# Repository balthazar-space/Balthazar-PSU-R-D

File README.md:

# Balthazar

Open-hardware laptop computer modules description and concept.

These are electronic schematic modules as presented at https://balthazar.space/wiki/Balthazar with the main aim for team access.
See the [main repository](https://github.com/balthazar-space/balthazar) for other designs.

# Balthazar PSU 

Module BalthazarPSU is a combined battery charger, buck-boost coverter and stereo power amplifier. 
KiCad 5.1.5 files can be found here.

## License

All resources licensed under the CERN Open Hardware Licence CERN-OHL W V.2.0

Version 2.0 of the CERN-OHL introduces three variants of the licence – strongly (S) reciprocal, weakly (W) reciprocal and permissive (P) – which aim to address specific constraints caused by different collaboration models currently used in open-hardware projects. 

The first two variants mean that if any product is made using an open hardware design, the design of that product, including any improvements or modifications, should be made available under the same licence as that of the original product. Permissive licences do not impose this condition.

See the [LICENSE.md](./LICENSE.md) file for more information.

## Funding

This project is funded through the [NGI Zero Entrust Fund](https://nlnet.nl/entrust), a fund
established by [NLnet](https://nlnet.nl) with financial support from the European Commission's
[Next Generation Internet](https://ngi.eu) program. Learn more on the [NLnet project page](https://nlnet.nl/project/Balthazar-Casing/).

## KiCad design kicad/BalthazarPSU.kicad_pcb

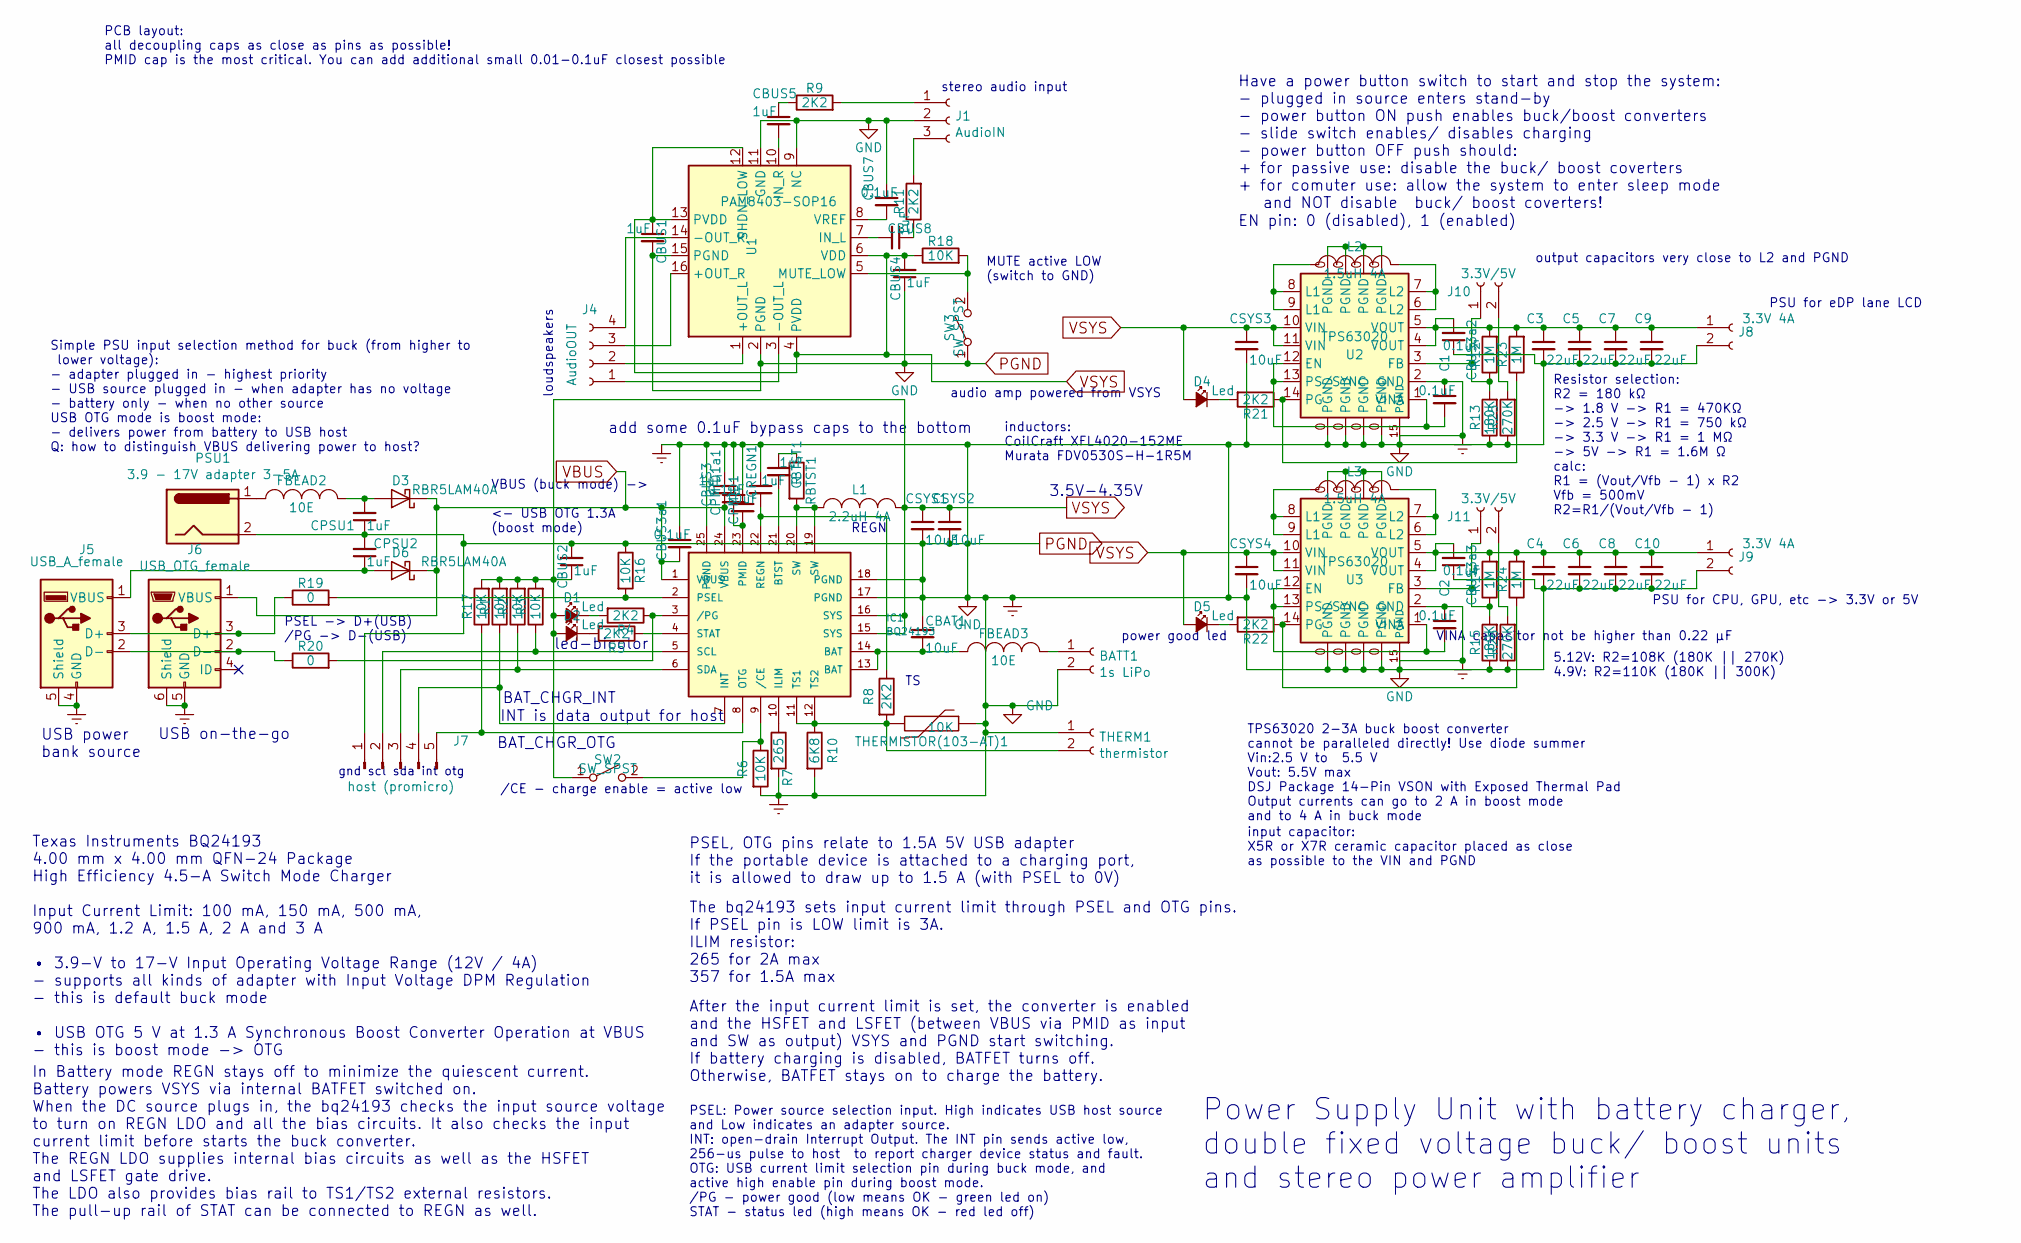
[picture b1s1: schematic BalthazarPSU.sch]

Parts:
BATT1: 1s LiPo; TerminalBlock_bornier-2_P5.08mm
C1, C2: 0.1uF; C_1206_3216Metric
C3, C4, C5, C6, C7, C8, C9, C10: 22uF; C_1206_3216Metric
CBAT1: 10uF; C_1206_3216Metric
CBTST1: 1uF; C_1206_3216Metric
CBUS1, CBUS2, CBUS3, CBUS4, CBUS5, CBUS8: 1uF; C_1206_3216Metric
CBUS3a1, CBUS3a2, CBUS3a3: 0.1uF; C_0805_2012Metric
CBUS7: 0.1uF; C_1206_3216Metric
CPMID1: 10uF; C_1206_3216Metric
CPMID1a1: 0.1uF; C_0805_2012Metric
CPSU1, CPSU2: 1uF; C_1206_3216Metric
CREGN1: 1uF; C_1206_3216Metric
CSYS1, CSYS2, CSYS3, CSYS4: 10uF; C_1206_3216Metric
D1, D2, D4, D5: Led; LED_1206_3216Metric
D3, D6: RBR5LAM40A; D_SOD-128
FBEAD2, FBEAD3: 10E; L_Neosid_MicroCoil_Ms36-L
IC1: BQ24193; QFN-24-1EP_4x4mm_P0.5mm_EP2.7x2.7mm_ThermalVias
J1: AudioIN; PinSocket_1x03_P2.54mm_Horizontal
J4: AudioOUT; PinSocket_1x04_P2.54mm_Horizontal
J5: USB_A_female; USB_A_CNCTech_1001-011-01101_Horizontal-Female
J6: USB_OTG_female; USB_Micro-B_Molex-105133-0031
J7: host (promicro); PinHeader_1x06_P2.54mm_Horizontal
J8, J9: 3.3V 4A; TerminalBlock_bornier-2_P5.08mm
J10, J11: 3.3V/5V; TestPoint_2Pads_Pitch2.54mm_Drill0.8mm
L1: 2.2uH 4A; L_Coilcraft_XxL4020
L2, L3: 1.5uH 4A; L_Coilcraft_XxL4020
PSU1: 3.9 - 17V adapter 3-5A; TerminalBlock_bornier-2_P5.08mm
R1, R2, R3, R6, R16, R17, R18: 10K; R_1206_3216Metric
R4, R5, R8, R9, R11, R21, R22: 2K2; R_1206_3216Metric
R7: 265; R_1206_3216Metric
R10: 6K8; R_1206_3216Metric
R12, R14, R23, R24: 1M; R_1206_3216Metric
R13, R15: 180K; R_1206_3216Metric
R19, R20: 0; R_1206_3216Metric
R25, R26: 270K; R_1206_3216Metric
RBTST1: R; R_1206_3216Metric
SW2, SW3: SW_SPST; SW_DIP_SPSTx01_Slide_6.7x4.1mm_W7.62mm_P2.54mm_LowProfile
THERM1: thermistor; TestPoint_2Pads_Pitch2.54mm_Drill0.8mm
THERMISTOR(103-AT)1: 10K; R_1206_3216Metric
U1: PAM8403-SOP16; SOP-16_4.4x10.4mm_P1.27mm
U2, U3: TPS63020; WSON-14-1EP_4.0x4.0mm_P0.5mm_EP2.6x2.6mmThermalPads

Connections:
unnamed: BATT1.1, FBEAD3.2
unnamed: C1.2, U2.1 (VINA), U2.12 (EN), U2.13 (PS/SYNC)
unnamed: C2.2, U3.1 (VINA), U3.12 (EN), U3.13 (PS/SYNC)
unnamed: C3.1, C5.1, C7.1, C9.1, CBUS3a2.2, J8.1, R12.2, R23.2, U2.4 (VOUT), U2.5 (VOUT)
unnamed: C4.1, C6.1, C8.1, C10.1, CBUS3a3.2, J9.1, R14.2, R24.2, U3.4 (VOUT), U3.5 (VOUT)
unnamed: CBAT1.2, FBEAD3.1, IC1.13 (BAT), IC1.14 (BAT)
unnamed: CBTST1.1, RBTST1.1
unnamed: CBTST1.2, IC1.21 (BTST)
unnamed: CBUS5.1, R9.1
unnamed: CBUS5.2, U1.10 (IN_R)
unnamed: CBUS7.2, U1.8 (VREF)
unnamed: CBUS8.1, R11.1
unnamed: CBUS8.2, U1.7 (IN_L)
unnamed: CPMID1.2, CPMID1a1.2, IC1.23 (PMID)
unnamed: CPSU1.2, D3.2 (A), FBEAD2.2
unnamed: CPSU2.1, D6.2 (A), J5.1 (VBUS)
unnamed: CREGN1.2, IC1.22 (REGN), R8.1
unnamed: D1.2 (C), R4.2
unnamed: D2.2 (C), R5.2
unnamed: D4.2 (C), R21.2
unnamed: D5.2 (C), R22.2
unnamed: FBEAD2.1, PSU1.1
unnamed: IC1.2 (PSEL), R16.2, R19.2
unnamed: IC1.3 (/PG), R4.1, R20.2
unnamed: IC1.4 (STAT), R5.1
unnamed: IC1.5 (SCL), J7.2, R3.1
unnamed: IC1.6 (SDA), J7.3, R2.1
unnamed: IC1.7 (INT), J7.4, R1.1
unnamed: IC1.8 (OTG), J7.5, R17.1
unnamed: IC1.9 (/CE), R6.1, SW2.2 (B)
unnamed: IC1.10 (ILIM), R7.1
unnamed: IC1.11 (TS1), IC1.12 (TS2), R8.2, R10.1, THERM1.2, THERMISTOR(103-AT)1.2
unnamed: IC1.19 (SW), IC1.20 (SW), L1.1, RBTST1.2
unnamed: J1.1, R9.2
unnamed: J1.3, R11.2
unnamed: J4.1, U1.3 (-OUT_L)
unnamed: J4.2, U1.1 (+OUT_L)
unnamed: J4.3, U1.16 (+OUT_R)
unnamed: J4.4, U1.14 (-OUT_R)
unnamed: J5.2 (D-), J6.2 (D-), R20.1
unnamed: J5.3 (D+), J6.3 (D+), R19.1
unnamed: J10.1, R12.1, R13.2, U2.3 (FB)
unnamed: J10.2, R25.2
unnamed: J11.1, R14.1, R15.2, U3.3 (FB)
unnamed: J11.2, R26.2
unnamed: L2.1, U2.8 (L1), U2.9 (L1)
unnamed: L2.2, U2.6 (L2), U2.7 (L2)
unnamed: L3.1, U3.8 (L1), U3.9 (L1)
unnamed: L3.2, U3.6 (L2), U3.7 (L2)
unnamed: R18.2, SW3.2 (B), U1.5 (MUTE_LOW)
unnamed: R21.1, R23.1, U2.14 (PG)
unnamed: R22.1, R24.1, U3.14 (PG)
VBUS: CBUS3.2, CBUS3a1.2, D3.1 (K), D6.1 (K), IC1.1 (VBUS), IC1.24 (VBUS), J6.1 (VBUS)
VSYS: CBUS1.1, CBUS2.1, CBUS4.2, CSYS1.1, CSYS2.1, CSYS3.1, CSYS4.1, D1.1 (A), D2.1 (A), D4.1 (A), D5.1 (A), IC1.15 (SYS), IC1.16 (SYS), L1.2, R1.2, R2.2, R3.2, R17.2, R18.1, SW2.1 (A), U1.4 (PVDD), U1.6 (VDD), U1.12 (SHDN_LOW), U1.13 (PVDD), U2.10 (VIN), U2.11 (VIN), U3.10 (VIN), U3.11 (VIN)

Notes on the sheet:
3.5V-4.35V
USB on-the-go
led-bicolor
BAT_CHGR_INT
BAT_CHGR_OTG
INT is data output for host
Texas Instruments BQ24193 4.00 mm x 4.00 mm QFN-24 Package High Efficiency 4.5-A Switch Mode Charger Input Current Limit: 100 mA, 150 mA, 500 mA, 900 mA, 1.2 A, 1.5 A, 2 A and 3 A • 3.9-V to 17-V Input Operating Voltage Range (12V / 4A) - supports all kinds of adapter with Input Voltage DPM Regulat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
PSEL, OTG pins relate to 1.5A 5V USB adapter If the portable device is attached to a charging port, it is allowed to draw up to 1.5 A (with PSEL to 0V)
In Battery mode REGN stays off to minimize the quiescent current. Battery powers VSYS via internal BATFET switched on. When the DC source plugs in, the bq24193 checks the input source voltage to turn on REGN LDO and all the bias circuits. It also checks the input current limit before starts the buc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
The bq24193 sets input current limit through PSEL and OTG pins. If PSEL pin is LOW limit is 3A. ILIM resistor: 265 for 2A max 357 for 1.5A max
After the input current limit is set, the converter is enabled and the HSFET and LSFET (between VBUS via PMID as input and SW as output) VSYS and PGND start switching. If battery charging is disabled, BATFET turns off. Otherwise, BATFET stays on to charge the battery.
PSU for CPU, GPU, etc -> 3.3V or 5V
TPS63020 2-3A buck boost converter cannot be paralleled directly! Use diode summer Vin:2.5 V to 5.5 V Vout: 5.5V max DSJ Package 14-Pin VSON with Exposed Thermal Pad Output currents can go to 2 A in boost mode and to 4 A in buck mode
inductors: CoilCraft XFL4020-152ME Murata FDV0530S-H-1R5M
Resistor selection: R2 = 180 kΩ -> 1.8 V -> R1 = 470KΩ -> 2.5 V -> R1 = 750 kΩ -> 3.3 V -> R1 = 1 MΩ -> 5V -> R1 = 1.6M Ω calc: R1 = (Vout/Vfb - 1) x R2 Vfb = 500mV R2=R1/(Vout/Vfb - 1)
REGN
stereo audio input
loudspeakers
MUTE active LOW (switch to GND)
/CE - charge enable = active low
PSEL: Power source selection input. High indicates USB host source and Low indicates an adapter source. INT: open-drain Interrupt Output. The INT pin sends active low, 256-us pulse to host to report charger device status and fault. OTG: USB current limit selection pin during buck mode, and active h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
PSEL -> D+(USB) /PG -> D-(USB)
Power Supply Unit with battery charger, double fixed voltage buck/ boost units and stereo power amplifier
PCB layout: all decoupling caps as close as pins as possible! PMID cap is the most critical. You can add additional small 0.01-0.1uF closest possible
PSU for eDP lane LCD
audio amp powered from VSYS
VBUS (buck mode) -> <- USB OTG 1.3A (boost mode)
Simple PSU input selection method for buck (from higher to lower voltage): - adapter plugged in - highest priority - USB source plugged in - when adapter has no voltage - battery only - when no other source USB OTG mode is boost mode: - delivers power from battery to USB host Q: how to distinguish 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
output capacitors very close to L2 and PGND
input capacitor: X5R or X7R ceramic capacitor placed as close as possible to the VIN and PGND
VINA capacitor not be higher than 0.22 μF
power good led
5.12V: R2=108K (180K || 270K) 4.9V: R2=110K (180K || 300K)
USB power bank source
gnd scl sda int otg
add some 0.1uF bypass caps to the bottom
EN pin: 0 (disabled), 1 (enabled)
Have a power button switch to start and stop the system: - plugged in source enters stand-by - power button ON push enables buck/boost converters - slide switch enables/ disables charging - power button OFF push should: + for passive use: disable the buck/ boost coverters + for comuter use: allow t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

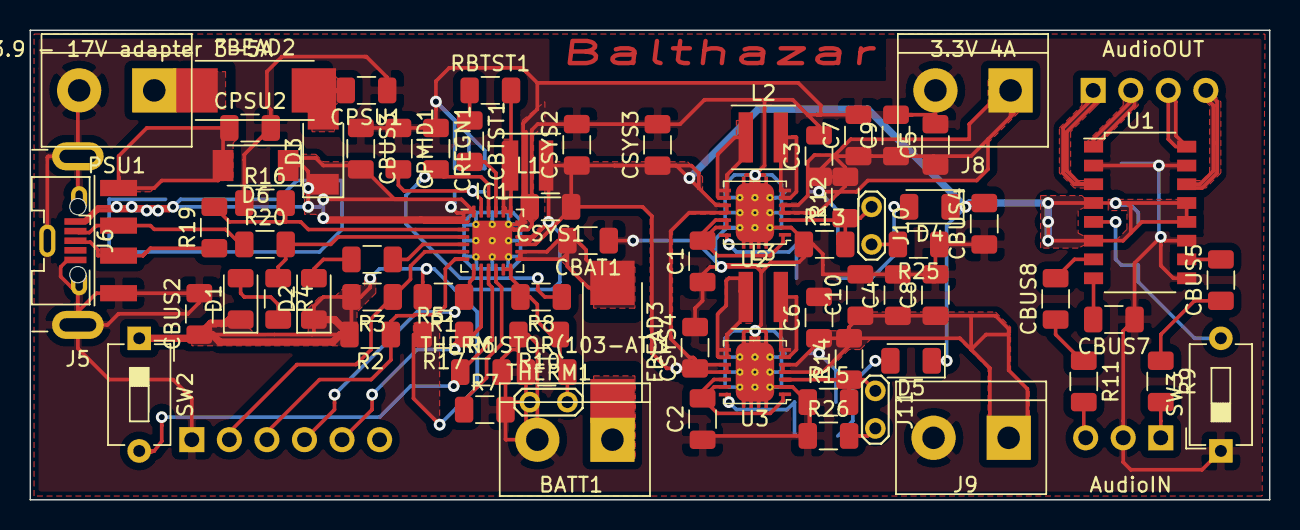
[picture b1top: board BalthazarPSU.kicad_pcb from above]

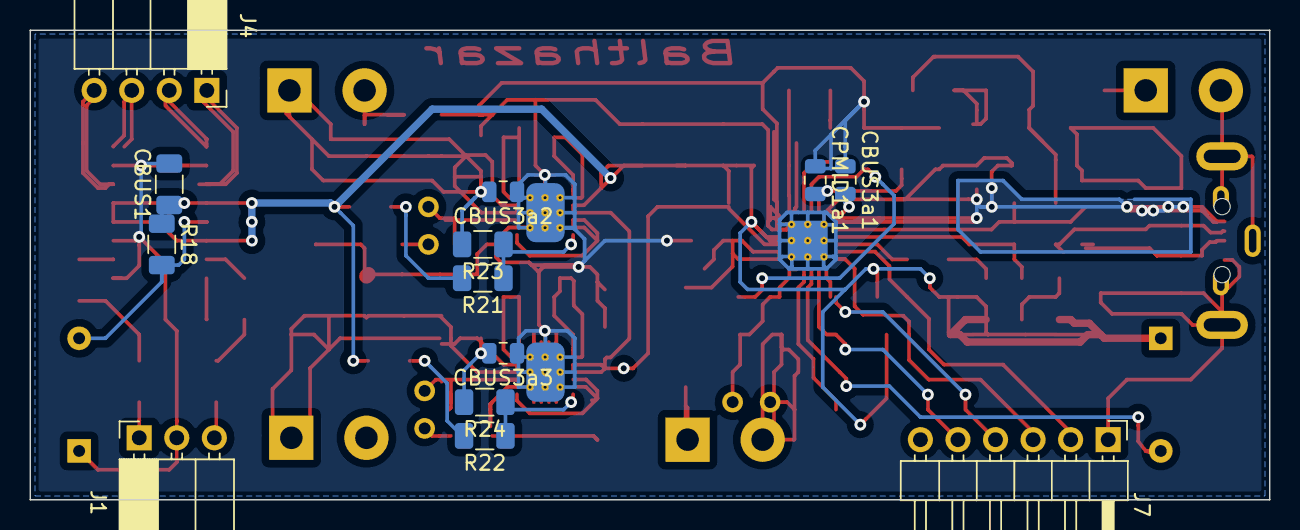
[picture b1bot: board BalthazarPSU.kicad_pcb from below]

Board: 2 copper layers, 83.8 x 31.8 mm, 88 parts (13 on the bottom side), 55 nets.

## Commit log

2020-06-19 NGI0-FSFE: Updating license file to include full license text
2021-07-28 admin
2024-06-25 Readme update
2024-06-25 Minor readme update for consistency
